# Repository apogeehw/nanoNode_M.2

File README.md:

# nanoNode_M.2
<br>
The official design repository for the nanoNode_M.2.

<br>

# Regulatory Notice:

### This is an engineering development board intended for research and prototyping. It is not a consumer product. The end-user is responsible for ensuring any final system integration complies with applicable FCC Part 15 regulations.

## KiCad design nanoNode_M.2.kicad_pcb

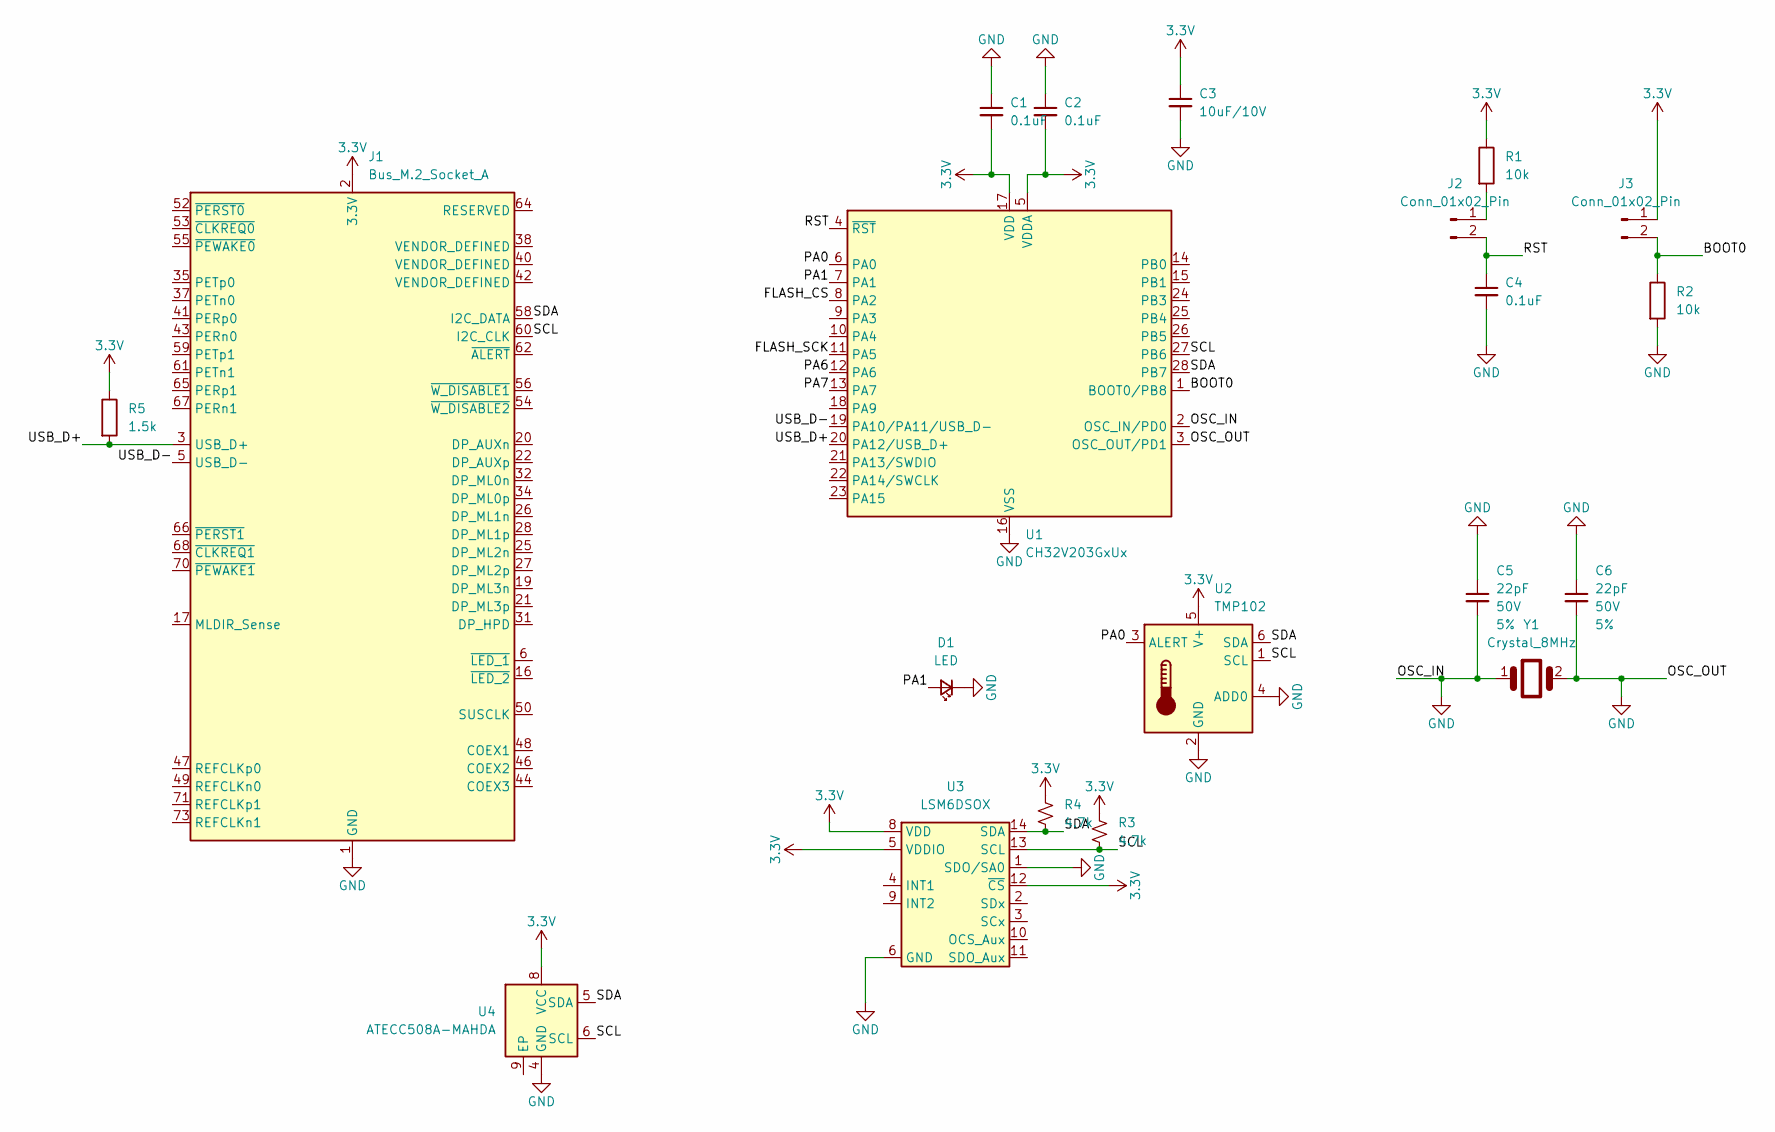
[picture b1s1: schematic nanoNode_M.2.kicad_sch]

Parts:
C1, C2, C4: 100nF_0603_16V; C_0201_0603Metric; Part Number 0603YC104KAT2A; JLCPCB ID C14663
C3: 10uF_0603_10V; C_0201_0603Metric; Part Number GRM188R61A106KE69D; JLCPCB ID C19702
C5, C6: 22pF; C_0402_1005Metric; Voltage 50V; Tolerance 5%
D1: LED; LED_0603_1608Metric
J1: Bus_M.2_Socket_A; M.2_2230-xx-A
J2, J3: Conn_01x02_Pin; PinHeader_1x02_P1.27mm_Vertical
R1, R2: 10k_0402; R_0402_1005Metric; Part Number RT0402FRE0710KL
R3, R4: 4.7k; R_0402_1005Metric
R5: 1.5k_0603; C_0201_0603Metric; Part Number RC0603FR-071K5L
U1: CH32V203GxUx; WQFN-28-1EP_4x4mm_P0.4mm_EP2.7x2.7mm
U2: TMP102; SOT-563
U3: LSM6DSOX; ST_LGA-14L_2.5x3.0mm_P0.5mm_4x3
U4: ATECC508A-MAHDA; DFN-8-1EP_3x2mm_P0.5mm_EP1.3x1.5mm
Y1: Crystal_8MHz; Crystal_SMD_0603-2Pin_6.0x3.5mm

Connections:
3.3V: C1.2, C2.2, C3.1, J1.2 (3.3V), J1.4 (3.3V), J1.72 (3.3V), J1.74 (3.3V), J3.1, R1.1, R3.2, R4.2, R5.1, U1.5 (VDDA), U1.17 (VDD), U2.5 (V+), U3.5 (VDDIO), U3.8 (VDD), U3.12 (~CS), U4.8 (VCC)
/BOOT0: J3.2, R2.1, U1.1 (BOOT0/PB8)
/FLASH_CS: U1.8 (PA2)
/FLASH_SCK: U1.11 (PA5)
/PA0: U1.6 (PA0), U2.3 (ALERT)
/PA1: D1.2 (A), U1.7 (PA1)
/PA6: U1.12 (PA6)
/PA7: U1.13 (PA7)
/RST: C4.1, J2.2, U1.4 (~RST)
/SCL: J1.60 (I2C_CLK), R3.1, U1.27 (PB6), U2.1 (SCL), U3.13 (SCL), U4.6 (SCL)
/SDA: J1.58 (I2C_DATA), R4.1, U1.28 (PB7), U2.6 (SDA), U3.14 (SDA), U4.5 (SDA)
/USB_D+: J1.3 (USB_D+), R5.2, U1.20 (PA12/USB_D+)
/USB_D-: J1.5 (USB_D-), U1.19 (PA10/PA11/USB_D-)
GND: C1.1, C2.1, C3.2, C4.2, C5.1, C5.2, C6.1, C6.2, D1.1 (K), J1.1 (GND), J1.7 (GND), J1.18 (GND), J1.23 (GND), J1.24 (GND), J1.29 (GND), J1.30 (GND), J1.33 (GND), J1.36 (GND), J1.39 (GND), J1.45 (GND), J1.51 (GND), J1.57 (GND), J1.63 (GND), J1.69 (GND), J1.75 (GND), R2.2, U1.2 (OSC_IN/PD0), U1.3 (OSC_OUT/PD1), U1.16 (VSS), U1.29 (VSS), U2.2 (GND), U2.4 (ADD0), U3.1 (SDO/SA0), U3.6 (GND), U3.7 (GND), U4.4 (GND), Y1.1, Y1.2
unnamed: J2.1, R1.2

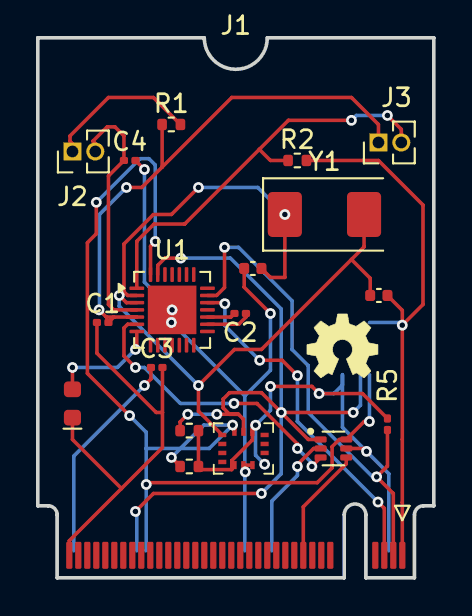
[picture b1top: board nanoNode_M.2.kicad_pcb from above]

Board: 2 copper layers, 22.0 x 30.0 mm, 21 parts (1 on the bottom side), 11 nets.

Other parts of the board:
Ref**: Val**; OSHW_Logo_4mm

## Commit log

2026-06-11 init
2026-06-11 README and License
2026-06-11 update and gitignore
